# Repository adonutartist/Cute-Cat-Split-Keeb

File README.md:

# nemoPAD V1

A wireless split mechanical keyboard with per key kalih hotswap sockets, per key underglow RGB, a slide potentiometer for brightness control on the right half, and a rotary encoder for volume control on the left half. Uses a sandwich mount case (bottom case + plate + top frame) held together with heatset inserts and m2 20mm screws. The CAD features a unique design so it can join up to change into a full keeb visually. A project by Nemo made for Forge YSWS by Hackclub.

NOTE TO REVIEWER: I didn't make an assembly with case PCB and all components because Importing PCB into onshape was way too laggy and crashed, Adding lots of components also made onshape lag like crazy and crash so I abandoned doing that I hope you understand. I have a potato laptop from 2020 its really a budget laptop so please understand... 

## Useful links
- **Total time spent:** [56h 2m](https://hackatime.hackclub.com/@Nemo_Donut/project/Keeb)
- **Devlogs:** [`JOURNAL.md`](./JOURNAL.md)
- **Onshape:** [CAD part of the project](https://cad.onshape.com/documents/d864244cbdf9531af3bfa9a7/w/1dab6020ee26630806b280f9/e/8f26d1999df9f3097243071e)

## Features
- Wireless split halves, each with its own XIAO nRF52840 MCU and LiPo battery
- Full hotswap (Kailh CPG151101S11 sockets), no soldering required for switches
- Per key RGB backlight using reverse mount underglow (SK6812MINI-E)
- MCP23017 I2C GPIO expander per half for full matrix coverage
- Slide potentiometer (right half) for brightness
- Rotary encoder with push (left half) for volume
- Sandwich mount case: top frame + plate + bottom case, screwed together with heatset inserts and m2 20mm screws

## Images
- Full 3D model render of the assembled keyboard (both halves)

- PCB render/photo with components populated (both halves)

- Schematic screenshots (1st image is left and 2nd image is right)

- Exploded view of the sandwich mount stack (bottom case / plate / top frame)

- Decal logo, custom encoder knob and hackclub logo emboss

## From concept to CAD
<p align="center">
  
  &nbsp;&nbsp;&nbsp;&nbsp;➡️&nbsp;&nbsp;&nbsp;&nbsp;
  
</p>

## Hardware design

### Sandwich mount stackup
| Layer | Thickness | Notes |
|---|---|---|
| Top frame | 6.3mm | Blind hole Ø3.5mm, 4.6mm deep for the heatset insert, no hole visible from outside |
| Plate | 1.5mm | Through hole Ø2.4mm for screw clearance |
| PCB | 1.6mm | |
| Bottom case (inner wall height) | 8mm | Clears the 3.05mm tall hotswap socket + ~3.16mm USB-C connector on the back layer with margin |
| Bottom case (bottom wall) | 3mm | Ø2.4mm x 1.2mm countersink on the underside so the screw head sits flush |

**Case is attached using** M2 x 4mm x 3.8mm OD brass heatset insert, M2 x 20mm countersunk screw.

**Battery pocket:** a local recessed pocket under the battery footprint on the inside of the bottom wall of bottom case (battery is the tallest bottom side component at ~5mm, taller than the general 6mm clearance zone needs). Battery wires are direct soldered to the BAT/GND test points, no connector.

## Bill of Materials
See [`BOM.csv`](./BOM.csv) for the full parts list with references, footprints, product links, and important notes.

### Summarised version:

| Component | Quantity | Total Price |
|---|---|---|
| 1N914 Diodes | 68 | ₹ 159.80 / $1.69 |
| SK6812MINI-E LEDs | 70 | ₹ 619.20 / $6.56 |
| 8.2k Resistor | 2 | ₹ 10.26 / $0.11 |
| 10k Resistor | 2 | ₹ 10.08 / $0.11 |
| Bourns Slide Potentiometer | 1 | ₹ 286.78 / $3.04 |
| Alps EC11E Rotary Encoder | 1 | NA (reused from kit) |
| Kailh Hotswap Sockets (all sizes) | 68 | ₹ 350.00 / $3.71 |
| MX-style Switches (all sizes) | 68 | ₹ 2,598.00 / $27.51 |
| Keycaps – 1u | 60 | ₹ 1,020.00 / $10.80 |
| Keycaps – 1.75u | 4 | ₹ 180.00 / $1.91 |
| Keycaps – 1.5u | 2 | ₹ 180.00 / $1.91 |
| Keycaps – 1.25u | 2 | NA (3D printed) |
| MCP23017 GPIO Expander | 2 | ₹ 539.00 / $5.71 |
| XIAO nRF52840 (modified) | 2 | ₹ 2,418.00 / $25.60 |
| LiPo Battery 500mAh | 2 | ₹ 476.98 / $5.05 |
| PCB (2-layer panel) | 5 | ₹ 5,003.00 / $52.97 |
| Heatset Insert | 8 | ₹ 108.65 / $1.15 |
| Case Screw | 8 | (included above) |
| 3D Printed Parts (case, plate, frame, knob, keycap) | 7 | ₹ 1,956.06 / $20.71 |
| **GRAND TOTAL** | | **₹ 15,915.81 / $168.51** |

## Assembly
1. Solder components to both PCB halves (or have them assembled), separate the panel at the mousebite tabs
2. Solder battery leads to BAT/GND test points on each half
3. Insert hotswap sockets, install switches
4. Heatset the M2 inserts into each top frame's blind holes
5. Sandwich bottom case -> PCB -> plate -> top frame, secure with M2x18mm screws
6. Flahing steps still needs work.

## Flashing

The keyboard uses two Seeed XIAO nRF52840 boards, one for each half. Separate firmware files are provided for the left and right halves.

### Requirements

* USB-C data cable
* Computer
* The appropriate `.uf2` firmware file

### Flash the Left Half

1. Connect the **left-half XIAO nRF52840** to your computer via USB.
2. Double-click the XIAO's **Reset** button to enter bootloader mode.
3. A USB mass-storage drive should appear.
4. Copy `zmk_left.uf2` onto the bootloader drive (Found inside Firmware folder).
5. The XIAO will automatically reboot after the firmware is copied.

### Flash the Right Half

1. Connect the **right-half XIAO nRF52840** to your computer via USB.
2. Double-click the XIAO's **Reset** button to enter bootloader mode.
3. A USB mass-storage drive should appear.
4. Copy `zmk_right.uf2` onto the bootloader drive (Found inside Firmware folder).
5. The XIAO will automatically reboot after the firmware is copied.

### Firmware Source

The firmware is built using **ZMK** with the Seeed XIAO nRF52840 target.

The provided firmware files are:

```text
Firmware/
├── zmk_left.uf2
└── zmk_right.uf2
```

The firmware currently represents the development stage prototype. Both left and right firmware builds complete successfully; physical flashing and keyboard testing will be performed once the PCBs and components are available.

---

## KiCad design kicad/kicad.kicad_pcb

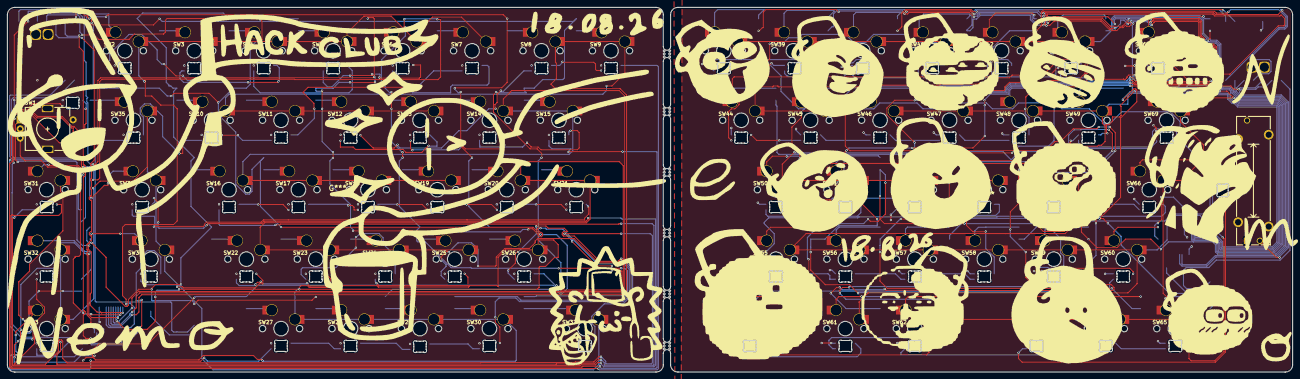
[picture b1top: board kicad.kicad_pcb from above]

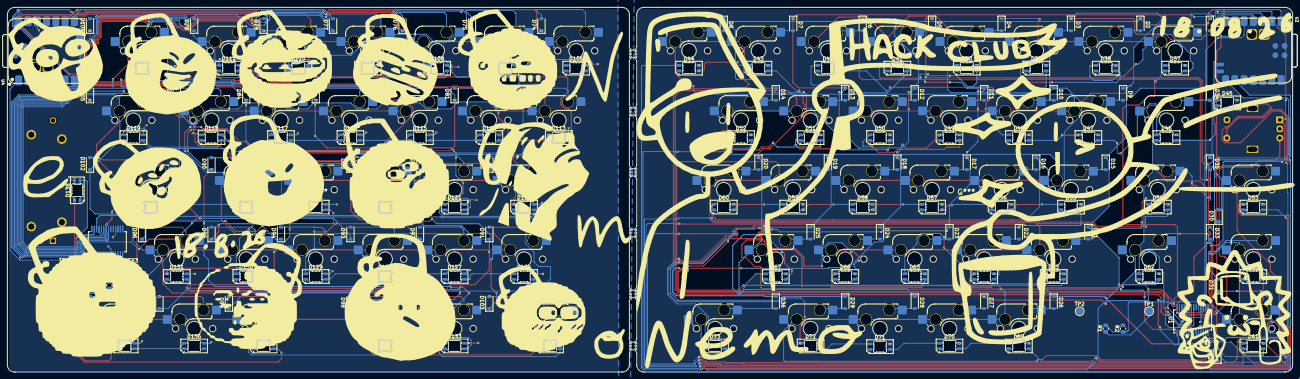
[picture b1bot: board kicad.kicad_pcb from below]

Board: 2 copper layers, 352.5 x 100.0 mm, 220 parts (150 on the bottom side), 174 nets.

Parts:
D1, D2, D3, D4, D5, D6, D7, D8, D9, D10, D11, D12, D13, D14, D15, D16, D17, D18, D19, D20, D21, D22, D23, D24, D25, D26, D27, D28, D29, D30, D31, D32, D33, D34, D35, D36, D74, D75, D76, D77, D78, D79, D80, D81, D82, D83, D84, D85, D86, D87, D88, D89, D90, D91, D92, D93, D94, D95, D96, D97, D98, D99, D100, D101, D102, D103, D104, D105: 1N914; D_SOD-123
D37, D38, D39, D40, D41, D42, D43, D44, D45, D46, D47, D48, D49, D50, D51, D52, D53, D54, D55, D56, D57, D58, D59, D60, D61, D62, D63, D64, D65, D66, D67, D68, D69, D70, D71, D72, D73, D106, D107, D108, D109, D110, D111, D112, D113, D114, D115, D116, D117, D118, D119, D120, D121, D122, D123, D124, D125, D126, D127, D128, D129, D130, D131, D132, D133, D134, D135, D136, D137, D138: SK6812MINI-E; LED_SK6812MINI-E_3.2x2.8mm_P1.5mm_ReverseMount
R1, R3: 806k; R_0805_2012Metric
R2, R4: 1M; R_0805_2012Metric
RV1: R_Potentiometer; Potentiometer_Bourns_PTA2043_Single_Slide
SW1: RotaryEncoder_Switch; RotaryEncoder_Alps_EC11E-Switch_Vertical_H20mm
SW2, SW3, SW4, SW5, SW6, SW7, SW8, SW9, SW10, SW11, SW12, SW13, SW14, SW15, SW16, SW17, SW18, SW19, SW20, SW21, SW22, SW23, SW24, SW25, SW26, SW27, SW28, SW29, SW30, SW31, SW32, SW33, SW38, SW39, SW40, SW41, SW42, SW43, SW44, SW45, SW46, SW47, SW48, SW49, SW50, SW51, SW52, SW53, SW54, SW55, SW56, SW57, SW58, SW59, SW60, SW61, SW62, SW63, SW64, SW65: SW_Push; hotswap_switches
SW34, SW37, SW66, SW67: SW_Push; SW_MX_HS_CPG151101S11_1.75u
SW35, SW69: SW_Push; SW_MX_HS_CPG151101S11_1.25u
SW36, SW68: SW_Push; SW_MX_HS_CPG151101S11_1.5u
TP1, TP3: BAT; TestPoint_Pad_D2.0mm
TP2, TP4: GND; TestPoint_Pad_D2.0mm
U1, U3: MCP23017x-x-SS; SSOP-28_5.3x10.2mm_P0.65mm
U2, U4: XIAO-nRF52840-SMD; modified-XIAO-nRF52840-SMD

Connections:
+3.3V: D37.3 (VDD), D38.3 (VDD), D39.3 (VDD), D40.3 (VDD), D41.3 (VDD), D42.3 (VDD), D43.3 (VDD), D44.3 (VDD), D45.3 (VDD), D46.3 (VDD), D47.3 (VDD), D48.3 (VDD), D49.3 (VDD), D50.3 (VDD), D51.3 (VDD), D52.3 (VDD), D53.3 (VDD), D54.3 (VDD), D55.3 (VDD), D56.3 (VDD), D57.3 (VDD), D58.3 (VDD), D59.3 (VDD), D60.3 (VDD), D61.3 (VDD), D62.3 (VDD), D63.3 (VDD), D64.3 (VDD), D65.3 (VDD), D66.3 (VDD), D67.3 (VDD), D68.3 (VDD), D69.3 (VDD), D70.3 (VDD), D71.3 (VDD), D72.3 (VDD), D73.3 (VDD), D106.3 (VDD), D107.3 (VDD), D108.3 (VDD), D109.3 (VDD), D110.3 (VDD), D111.3 (VDD), D112.3 (VDD), D113.3 (VDD), D114.3 (VDD), D115.3 (VDD), D116.3 (VDD), D117.3 (VDD), D118.3 (VDD), D119.3 (VDD), D120.3 (VDD), D121.3 (VDD), D122.3 (VDD), D123.3 (VDD), D124.3 (VDD), D125.3 (VDD), D126.3 (VDD), D127.3 (VDD), D128.3 (VDD), D129.3 (VDD), D130.3 (VDD), D131.3 (VDD), D132.3 (VDD), D133.3 (VDD), D134.3 (VDD), D135.3 (VDD), D136.3 (VDD), D137.3 (VDD), D138.3 (VDD), RV1.1, U1.9 (V_{DD}), U1.18 (~RESET), U2.12 (3V3), U3.9 (V_{DD}), U3.18 (~RESET), U4.12 (3V3)
/LEFT/BT_PIN: R1.2, R2.1, U2.1 (P0.02_A0_D0)
/LEFT/COL0: SW2.1, SW3.1, SW4.1, SW5.1, SW6.1, SW7.1, U1.21 (GPA0)
/LEFT/COL1: SW8.1, SW9.1, SW10.1, SW11.1, SW12.1, SW13.1, U1.22 (GPA1)
/LEFT/COL2: SW14.1, SW15.1, SW16.1, SW17.1, SW18.1, SW19.1, U1.23 (GPA2)
/LEFT/COL3: SW20.1, SW21.1, SW22.1, SW23.1, SW24.1, SW25.1, U1.24 (GPA3)
/LEFT/COL4: SW26.1, SW27.1, SW28.1, SW29.1, SW30.1, SW31.1, U1.25 (GPA4)
/LEFT/COL5: SW32.1, SW33.1, SW34.1, SW35.1, SW36.1, SW37.1, U1.26 (GPA5)
/LEFT/EA: SW1.A, U1.28 (GPA7)
/LEFT/EB: SW1.B, U1.27 (GPA6)
/LEFT/ES: SW1.S1, U1.1 (GPB0)
/LEFT/ROW0: D1.1 (K), D7.1 (K), D13.1 (K), D19.1 (K), D25.1 (K), D31.1 (K), U2.2 (P0.03_A1_D1)
/LEFT/ROW1: D2.1 (K), D8.1 (K), D14.1 (K), D20.1 (K), D26.1 (K), D32.1 (K), U2.3 (P0.28_A2_D2)
/LEFT/ROW2: D3.1 (K), D9.1 (K), D15.1 (K), D21.1 (K), D27.1 (K), D33.1 (K), U2.4 (P0.29_A3_D3)
/LEFT/ROW3: D4.1 (K), D10.1 (K), D16.1 (K), D22.1 (K), D28.1 (K), D34.1 (K), U2.7 (P1.11_D6_TX)
/LEFT/ROW4: D5.1 (K), D11.1 (K), D17.1 (K), D23.1 (K), D29.1 (K), D35.1 (K), U2.9 (P1.13_D8_SCK)
/LEFT/ROW5: D6.1 (K), D12.1 (K), D18.1 (K), D24.1 (K), D30.1 (K), D36.1 (K), U2.8 (P1.12_D7_RX)
/LEFT/SCL: U1.12 (SCK), U2.6 (P0.05_A5_D5_SCL)
/LEFT/SDA: U1.13 (SDA), U2.5 (P0.04_A4_D4_SDA)
/LEFT/VBAT: R1.1, TP1.1 (1_1)
/RIGHT/BT_PIN: R3.2, R4.1, U4.1 (P0.02_A0_D0)
/RIGHT/COL0: SW38.1, SW39.1, SW40.1, SW41.1, SW42.1, SW43.1, SW44.1, SW45.1, U3.24 (GPA3)
/RIGHT/COL1: SW46.1, SW47.1, SW48.1, SW49.1, SW50.1, SW51.1, SW52.1, SW53.1, U3.25 (GPA4)
/RIGHT/COL2: SW54.1, SW55.1, SW56.1, SW57.1, SW58.1, SW59.1, SW60.1, SW61.1, U3.26 (GPA5)
/RIGHT/COL3: SW62.1, SW63.1, SW64.1, SW65.1, SW66.1, SW67.1, SW68.1, SW69.1, U3.27 (GPA6)
/RIGHT/ROW0: D74.1 (K), D82.1 (K), D90.1 (K), D98.1 (K), U4.3 (P0.28_A2_D2)
/RIGHT/ROW1: D75.1 (K), D83.1 (K), D91.1 (K), D99.1 (K), U4.4 (P0.29_A3_D3)
/RIGHT/ROW2: D76.1 (K), D84.1 (K), D92.1 (K), D100.1 (K), U4.7 (P1.11_D6_TX)
/RIGHT/ROW3: D77.1 (K), D85.1 (K), D93.1 (K), D101.1 (K), U4.8 (P1.12_D7_RX)
/RIGHT/ROW4: D78.1 (K), D86.1 (K), D94.1 (K), D102.1 (K), U4.9 (P1.13_D8_SCK)
/RIGHT/ROW5: D79.1 (K), D87.1 (K), D95.1 (K), D103.1 (K), U3.21 (GPA0)
/RIGHT/ROW6: D80.1 (K), D88.1 (K), D96.1 (K), D104.1 (K), U3.22 (GPA1)
/RIGHT/ROW7: D81.1 (K), D89.1 (K), D97.1 (K), D105.1 (K), U3.23 (GPA2)
/RIGHT/SCL: U3.12 (SCK), U4.6 (P0.05_A5_D5_SCL)
/RIGHT/SDA: U3.13 (SDA), U4.5 (P0.04_A4_D4_SDA)
/RIGHT/Slider: RV1.2, U4.2 (P0.03_A1_D1)
/RIGHT/VBAT: R3.1, TP3.1 (1_1)
GND: D37.1 (VSS), D38.1 (VSS), D39.1 (VSS), D40.1 (VSS), D41.1 (VSS), D42.1 (VSS), D43.1 (VSS), D44.1 (VSS), D45.1 (VSS), D46.1 (VSS), D47.1 (VSS), D48.1 (VSS), D49.1 (VSS), D50.1 (VSS), D51.1 (VSS), D52.1 (VSS), D53.1 (VSS), D54.1 (VSS), D55.1 (VSS), D56.1 (VSS), D57.1 (VSS), D58.1 (VSS), D59.1 (VSS), D60.1 (VSS), D61.1 (VSS), D62.1 (VSS), D63.1 (VSS), D64.1 (VSS), D65.1 (VSS), D66.1 (VSS), D67.1 (VSS), D68.1 (VSS), D69.1 (VSS), D70.1 (VSS), D71.1 (VSS), D72.1 (VSS), D73.1 (VSS), D106.1 (VSS), D107.1 (VSS), D108.1 (VSS), D109.1 (VSS), D110.1 (VSS), D111.1 (VSS), D112.1 (VSS), D113.1 (VSS), D114.1 (VSS), D115.1 (VSS), D116.1 (VSS), D117.1 (VSS), D118.1 (VSS), D119.1 (VSS), D120.1 (VSS), D121.1 (VSS), D122.1 (VSS), D123.1 (VSS), D124.1 (VSS), D125.1 (VSS), D126.1 (VSS), D127.1 (VSS), D128.1 (VSS), D129.1 (VSS), D130.1 (VSS), D131.1 (VSS), D132.1 (VSS), D133.1 (VSS), D134.1 (VSS), D135.1 (VSS), D136.1 (VSS), D137.1 (VSS), D138.1 (VSS), R2.2, R4.2, RV1.3, SW1.C, SW1.S2, TP2.1 (1_1), TP4.1 (1_1), U1.10 (V_{SS}), U1.15 (A0), U1.16 (A1), U1.17 (A2), U2.13 (GND), U3.10 (V_{SS}), U3.15 (A0), U3.16 (A1), U3.17 (A2), U4.13 (GND)
unnamed: D1.2 (A), SW2.2
unnamed: D2.2 (A), SW3.2
unnamed: D3.2 (A), SW4.2
unnamed: D4.2 (A), SW5.2
unnamed: D5.2 (A), SW6.2
unnamed: D6.2 (A), SW7.2
unnamed: D7.2 (A), SW8.2
unnamed: D8.2 (A), SW9.2
unnamed: D9.2 (A), SW10.2
unnamed: D10.2 (A), SW11.2
unnamed: D11.2 (A), SW12.2
unnamed: D12.2 (A), SW13.2
unnamed: D13.2 (A), SW14.2
unnamed: D14.2 (A), SW15.2
unnamed: D15.2 (A), SW16.2
unnamed: D16.2 (A), SW17.2
unnamed: D17.2 (A), SW18.2
unnamed: D18.2 (A), SW19.2
unnamed: D19.2 (A), SW20.2
unnamed: D20.2 (A), SW21.2
unnamed: D21.2 (A), SW22.2
unnamed: D22.2 (A), SW23.2
unnamed: D23.2 (A), SW24.2
unnamed: D24.2 (A), SW25.2
unnamed: D25.2 (A), SW26.2
unnamed: D26.2 (A), SW27.2
unnamed: D27.2 (A), SW28.2
unnamed: D28.2 (A), SW29.2
unnamed: D29.2 (A), SW30.2
unnamed: D30.2 (A), SW31.2
unnamed: D31.2 (A), SW32.2
unnamed: D32.2 (A), SW33.2
unnamed: D33.2 (A), SW34.2
unnamed: D34.2 (A), SW35.2
unnamed: D35.2 (A), SW36.2
unnamed: D36.2 (A), SW37.2
unnamed: D37.4 (DOUT), D38.2 (DIN)
unnamed: D38.4 (DOUT), D39.2 (DIN)
unnamed: D39.4 (DOUT), D40.2 (DIN)
unnamed: D40.4 (DOUT), D41.2 (DIN)
unnamed: D41.4 (DOUT), D42.2 (DIN)
unnamed: D42.4 (DOUT), D48.2 (DIN)
unnamed: D43.2 (DIN), D44.4 (DOUT)
unnamed: D43.4 (DOUT), D49.2 (DIN)
unnamed: D44.2 (DIN), D45.4 (DOUT)
unnamed: D45.2 (DIN), D46.4 (DOUT)
unnamed: D46.2 (DIN), D47.4 (DOUT)
unnamed: D47.2 (DIN), D48.4 (DOUT)
unnamed: D49.4 (DOUT), D50.2 (DIN)
unnamed: D50.4 (DOUT), D51.2 (DIN)
unnamed: D51.4 (DOUT), D52.2 (DIN)
unnamed: D52.4 (DOUT), D53.2 (DIN)
unnamed: D53.4 (DOUT), D54.2 (DIN)
unnamed: D54.4 (DOUT), D60.2 (DIN)
unnamed: D55.2 (DIN), D56.4 (DOUT)
unnamed: D55.4 (DOUT), D61.2 (DIN)
unnamed: D56.2 (DIN), D57.4 (DOUT)
unnamed: D57.2 (DIN), D58.4 (DOUT)
unnamed: D58.2 (DIN), D59.4 (DOUT)
unnamed: D59.2 (DIN), D60.4 (DOUT)
unnamed: D61.4 (DOUT), D62.2 (DIN)
unnamed: D62.4 (DOUT), D63.2 (DIN)
unnamed: D63.4 (DOUT), D64.2 (DIN)
unnamed: D64.4 (DOUT), D65.2 (DIN)
unnamed: D65.4 (DOUT), D66.2 (DIN)
unnamed: D66.4 (DOUT), D72.2 (DIN)
unnamed: D67.2 (DIN), D68.4 (DOUT)
unnamed: D67.4 (DOUT), D73.2 (DIN)
unnamed: D68.2 (DIN), D69.4 (DOUT)
unnamed: D69.2 (DIN), D70.4 (DOUT)
unnamed: D70.2 (DIN), D71.4 (DOUT)
unnamed: D71.2 (DIN), D72.4 (DOUT)
unnamed: D74.2 (A), SW38.2
unnamed: D75.2 (A), SW39.2
unnamed: D76.2 (A), SW40.2
unnamed: D77.2 (A), SW41.2
unnamed: D78.2 (A), SW42.2
unnamed: D79.2 (A), SW43.2
unnamed: D80.2 (A), SW44.2
unnamed: D81.2 (A), SW45.2
unnamed: D82.2 (A), SW46.2
unnamed: D83.2 (A), SW47.2
unnamed: D84.2 (A), SW48.2
unnamed: D85.2 (A), SW49.2
unnamed: D86.2 (A), SW50.2
unnamed: D87.2 (A), SW51.2
unnamed: D88.2 (A), SW52.2
unnamed: D89.2 (A), SW53.2
unnamed: D90.2 (A), SW54.2
unnamed: D91.2 (A), SW55.2
unnamed: D92.2 (A), SW56.2
unnamed: D93.2 (A), SW57.2
unnamed: D94.2 (A), SW58.2
unnamed: D95.2 (A), SW59.2
unnamed: D96.2 (A), SW60.2
unnamed: D97.2 (A), SW61.2
unnamed: D98.2 (A), SW62.2
unnamed: D99.2 (A), SW63.2
unnamed: D100.2 (A), SW64.2
unnamed: D101.2 (A), SW65.2
unnamed: D102.2 (A), SW66.2
unnamed: D103.2 (A), SW67.2
unnamed: D104.2 (A), SW68.2
unnamed: D105.2 (A), SW69.2
unnamed: D106.4 (DOUT), D107.2 (DIN)
unnamed: D107.4 (DOUT), D108.2 (DIN)
unnamed: D108.4 (DOUT), D109.2 (DIN)
unnamed: D109.4 (DOUT), D110.2 (DIN)
unnamed: D110.4 (DOUT), D111.2 (DIN)
unnamed: D111.4 (DOUT), D117.2 (DIN)
unnamed: D112.2 (DIN), D113.4 (DOUT)
unnamed: D112.4 (DOUT), D118.2 (DIN)
unnamed: D113.2 (DIN), D114.4 (DOUT)
unnamed: D114.2 (DIN), D115.4 (DOUT)
unnamed: D115.2 (DIN), D116.4 (DOUT)
unnamed: D116.2 (DIN), D117.4 (DOUT)
unnamed: D118.4 (DOUT), D119.2 (DIN)
unnamed: D119.4 (DOUT), D120.2 (DIN)
unnamed: D120.4 (DOUT), D121.2 (DIN)
unnamed: D121.4 (DOUT), D122.2 (DIN)
unnamed: D122.4 (DOUT), D123.2 (DIN)
unnamed: D123.4 (DOUT), D129.2 (DIN)
unnamed: D124.2 (DIN), D125.4 (DOUT)
unnamed: D124.4 (DOUT), D130.2 (DIN)
unnamed: D125.2 (DIN), D126.4 (DOUT)
unnamed: D126.2 (DIN), D127.4 (DOUT)
unnamed: D127.2 (DIN), D128.4 (DOUT)
unnamed: D128.2 (DIN), D129.4 (DOUT)
unnamed: D130.4 (DOUT), D131.2 (DIN)
unnamed: D131.4 (DOUT), D132.2 (DIN)
unnamed: D132.4 (DOUT), D133.2 (DIN)
unnamed: D133.4 (DOUT), D134.2 (DIN)
unnamed: D134.4 (DOUT), D135.2 (DIN)
unnamed: D135.4 (DOUT), D138.2 (DIN)
unnamed: D136.2 (DIN), D137.4 (DOUT)
unnamed: D137.2 (DIN), D138.4 (DOUT)

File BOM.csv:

Category,Reference(s),Qty,Part / Value,Footprint / Package,Description,Datasheet / Link,Unit Price (INR),Total (INR),Notes
Electronics,"D1-D32 (left), D66-D101 (right)",68,1N914,SOD-123,Small signal switching diode (per-key),http://www.vishay.com/docs/85622/1n914.pdf,,,TODO: add vendor link + price
Electronics,"D33-D65 (left), D102-D138 (right)",70,SK6812MINI-E,LED_SK6812MINI-E_3.2x2.8mm ReverseMount,Per-key + underglow RGB LED (reverse mount = bottom side),https://www.lcsc.com/datasheet/C5149201.pdf,,,TODO: add vendor link + price
Electronics,"R1, R3",2,806k,0805,Battery voltage-divider resistor (top),,,,Pairs with R2/R4 for ADC battery read
Electronics,"R2, R4",2,1M,0805,Battery voltage-divider resistor (bottom),,,,
Electronics,RV1,1,Bourns PTA2043-2015DPB103,Potentiometer_Bourns_PTA2043_Single_Slide,"Slide potentiometer, 20mm travel, brightness/volume control (left half only)",https://www.bourns.com,,,Body 35x9x6.5mm; see plate cutout spec in README
Electronics,SW33,1,Alps EC11E,RotaryEncoder_Alps_EC11E-Switch_Vertical_H20mm,"Rotary encoder w/ push switch, 20mm vertical shaft (right half only)",,,,Needs plate + top frame cutout for shaft
Electronics,"SW1-28, SW34-65",60,SW_Push (1u),PCM_marbastlib-mx CPG151101S11 1u,Kailh hotswap socket - 1u keys,,,,Socket protrudes 3.05mm below PCB
Electronics,"SW29-30, SW66, SW69",4,SW_Push (1.75u),PCM_marbastlib-mx CPG151101S11 1.75u,Kailh hotswap socket - 1.75u keys,,,,
Electronics,"SW31, SW68",2,SW_Push (1.5u),PCM_marbastlib-mx CPG151101S11 1.5u,Kailh hotswap socket - 1.5u keys,,,,
Electronics,"SW32, SW67",2,SW_Push (1.25u),PCM_marbastlib-mx CPG151101S11 1.25u,Kailh hotswap socket - 1.25u keys,,,,
Electronics,TP1-TP4,4,TestPoint,TestPoint_Pad_D2.0mm,BAT/GND probe pads (2 per half); battery wires direct-soldered here,,,,No connector - direct solder per build guide
Electronics,"U1, U3",2,MCP23017,SSOP-28,16-bit I2C GPIO expander,https://ww1.microchip.com/downloads/aemDocuments/documents/A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,,,
Electronics,"U2, U4",2,Modified XIAO nRF52840 SMD,modified-XIAO-nRF52840-SMD (custom),"MCU, back layer of PCB, standard USB-C connector (~3.16mm tall)",,,,Custom footprint - not stock Seeed module
Power,Battery x2,2,LiPo 502535 500mAh,N/A,"One battery per half, direct-soldered to BAT/GND test points, sits in local case-floor recess",,,,TODO: confirm exact cell purchased + price
Fabrication,PCB (panel),1,2-layer PCB panel (L+R mousebite-panelized),N/A,Fabricated as single panel with mousebite tabs; snaps into left + right boards after fab,,,,TODO: add fab house link (Seeed Fusion per Forge India guide) + price
Mechanical,Heatset insert,TODO qty (est. 12 = 6/half),M2 x 4mm x 3.5mm OD,Brass knurled heatset insert,Installed in top frame blind holes (6.2mm deep),,,,TODO: confirm final screw-hole count per half
Mechanical,Case screw,TODO qty (est. 12 = 6/half),M2 x 18mm countersunk,Steel or A2 stainless,Bottom case -> plate -> top frame insert,,,,Length assumes 6mm case wall + 8mm top frame / see stackup notes in README
Mechanical,Bottom case,2 (1/half),Custom 3D print,N/A,3mm bottom wall + 6mm wall height + local battery-pocket boss,,,,Your own CAD/print
Mechanical,Plate,2 (1/half),Custom (FR4/PC),1.5mm,Switch mounting plate with screw clearance + pot/encoder cutouts,,,,Your own CAD/manufacture
Mechanical,Top frame,2 (1/half),Custom 3D print,8mm,"Holds heatset inserts, blind holes only (no visible top holes)",,,,Your own CAD/print
,,,,,,,,,
,,,,,,,,GRAND TOTAL,TODO - fill in once all vendor prices are added
